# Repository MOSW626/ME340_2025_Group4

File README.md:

# ME340_2025_Group4
`/application` 에는 애플리케이션 개발에 대한 내용 작성\
`/chair` 에는 의자 관련 내용 작성\
  ㄴ 아두이노\
  ㄴ 하드웨어 설계\
  ㄴ 회로 설계\
`\detected_machine` 에는 몸 관련 측정 센서 내용 작성\
  ㄴ 아두이노(src)\
  ㄴ 하드웨어 설계\
  ㄴ 회로 설계

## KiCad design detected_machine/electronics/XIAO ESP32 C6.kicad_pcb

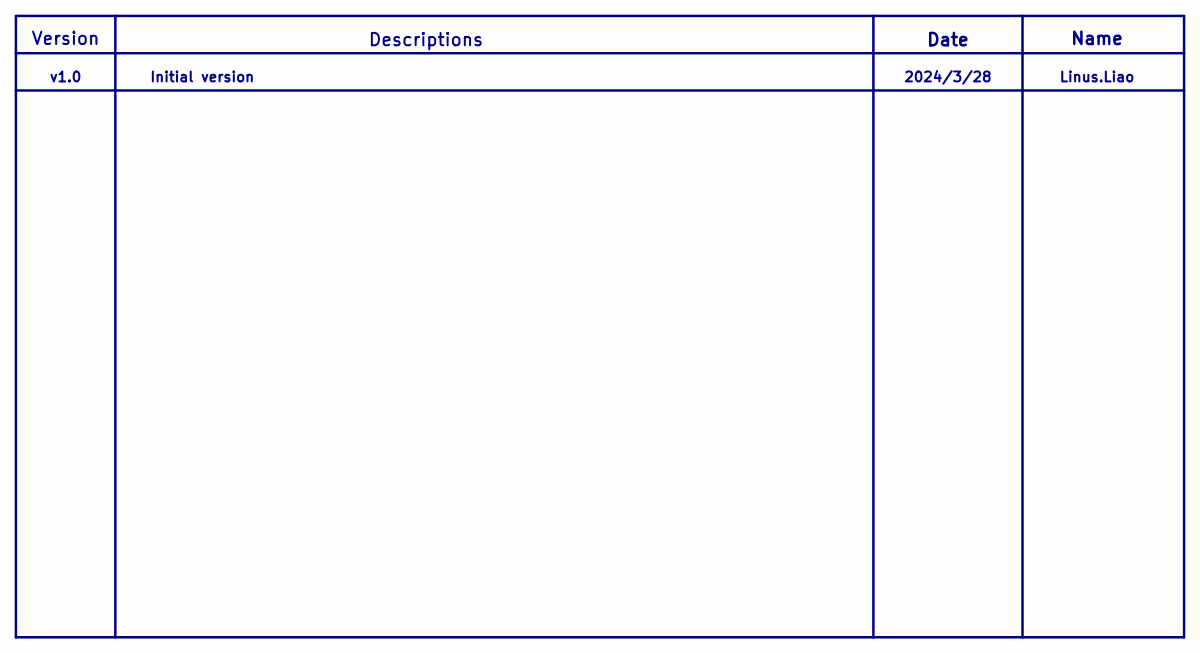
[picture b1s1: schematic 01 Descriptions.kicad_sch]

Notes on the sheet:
Date
Descriptions
Linus.Liao
2024/3/28
v1.0
Initial version
Name
Version

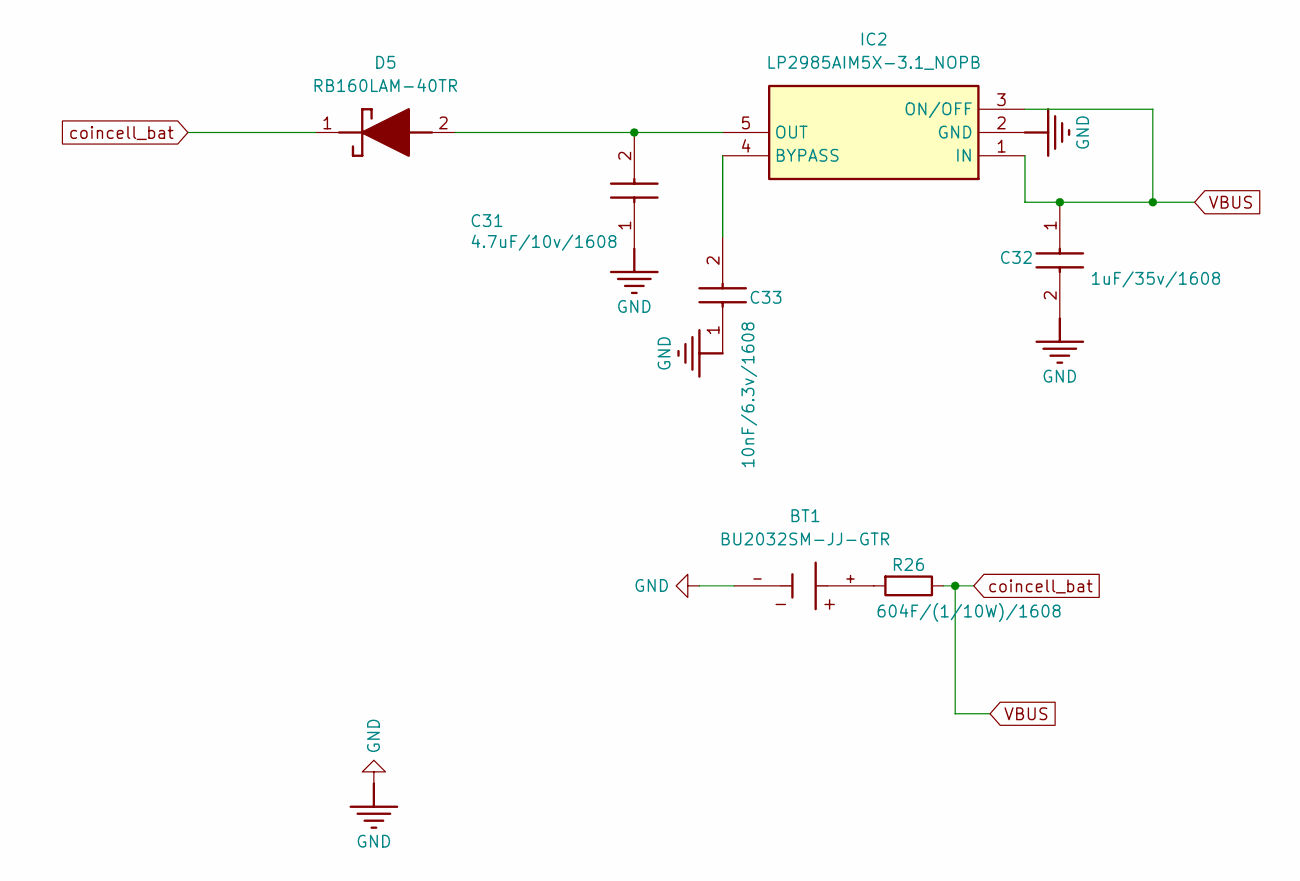
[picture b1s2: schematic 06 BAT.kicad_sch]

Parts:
BT1: BU2032SM-JJ-GTR; BAT_BU2032SM-JJ-GTR; PARTREV H
C31: 4.7uF/10v/1608; C_0603_1608Metric; MANUFACTURER_PART_NUMBER GRM188C71A475KE11D
C32: 1uF/35v/1608; C_0603_1608Metric; MANUFACTURER_PART_NUMBER MBASG168AB7105KTNA01
C33: 10nF/6.3v/1608; C_0603_1608Metric; MANUFACTURER_PART_NUMBER 06036C103KAT2A
D5: RB160LAM-40TR; SODFL4725X105N; Mouser Part Number 755-RB160LAM-40TR
IC2: LP2985AIM5X-3.1_NOPB; SOT95P280X145-5N; Mouser Part Number 926-LP2985AIM5X31NPB
R26: 604F/(1/10W)/1608; R_0603_1608Metric; MANUFACTURER_PART_NUMBER CRCW0603604RFKEAC

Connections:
GND: BT1.-, C31.1, C32.2, C33.1, IC2.2 (GND); also elsewhere on the board
unnamed: BT1.+, R26.2
unnamed: C31.2, D5.2 (A), IC2.5 (OUT)
unnamed: C33.2, IC2.4 (BYPASS)
VBUS: C32.1, D5.1 (K), IC2.1 (IN), IC2.3 (ON/OFF), R26.1; also elsewhere on the board

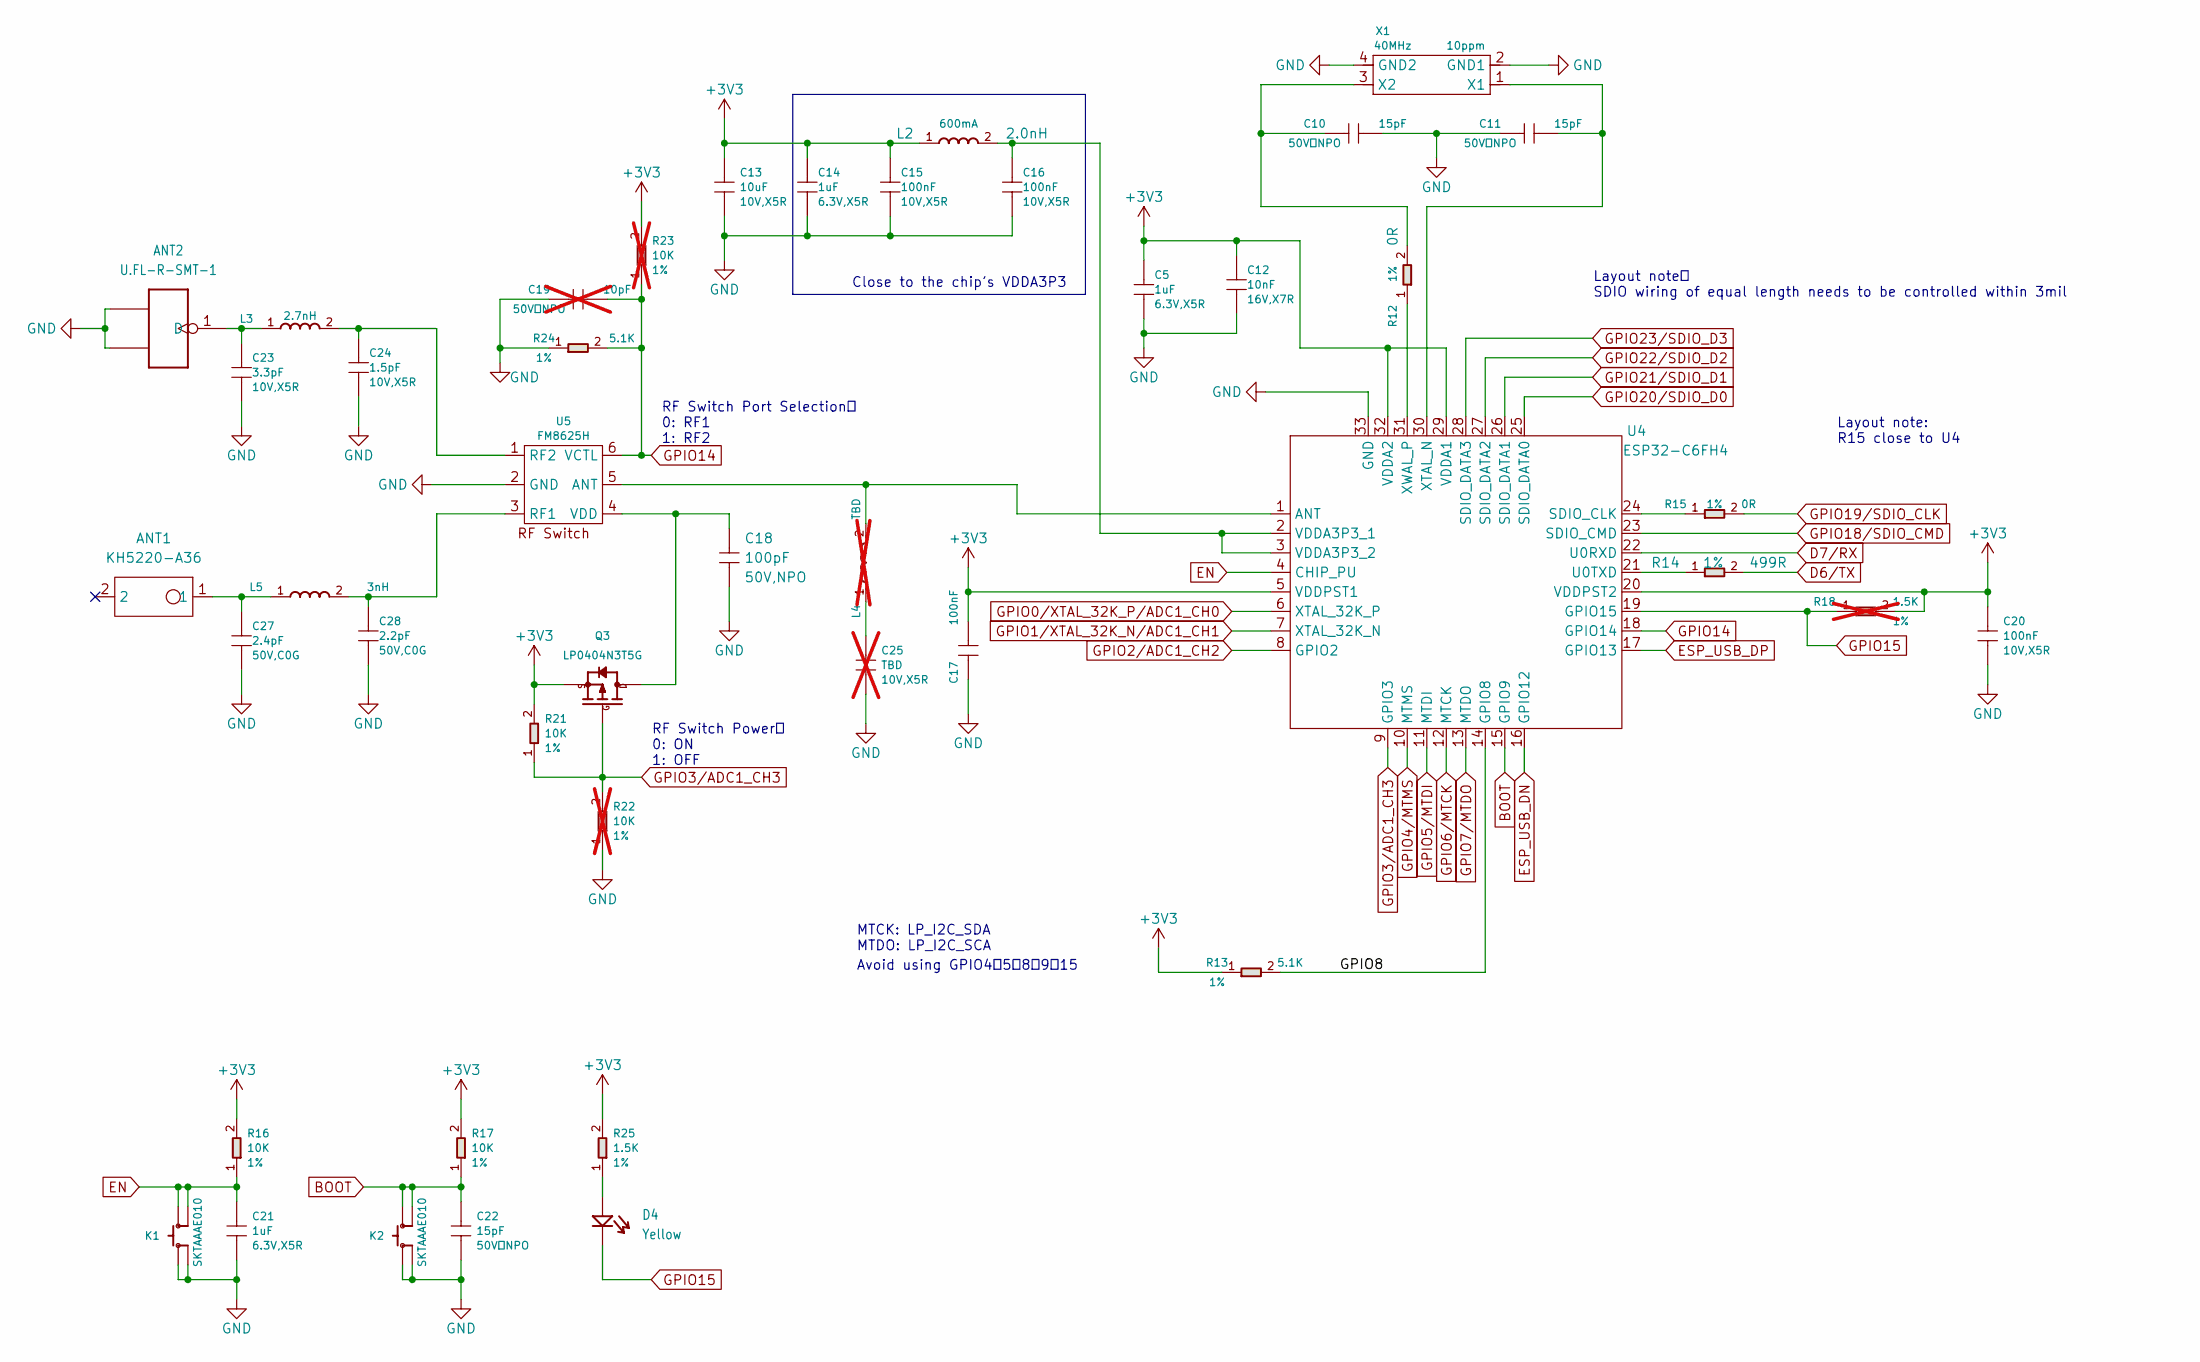
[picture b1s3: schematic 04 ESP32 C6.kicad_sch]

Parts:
ANT1: KH5220-A36; ANT2P-5.2x2x1.1MM; MPN KH5220-A36
ANT2: U.FL-R-SMT-1; U-FL3P-SMD-2.6X2.6X1.0MM; MPN U.FL-R-SMT-1
C5, C14, C21: 1uF; C0201; Voltage Rating 6.3V,X5R; MPN CC0201MRX5R5BB105
C10, C11, C22: 15pF; C0201; Voltage Rating 50V，NPO; MPN CC0201JRNPO9BN150
C12: 10nF; C0201; Voltage Rating 16V,X7R; MPN CC0201KRX7R7BB103
C13: 10uF; C0402; Voltage Rating 10V,X5R; MPN CC0402MRX5R6BB106
C15, C16, C17, C20: 100nF; C0201; Voltage Rating 10V,X5R; MPN CC0201KRX5R6BB104
C18: 100pF; C0201; Voltage Rating 50V,NPO; MPN CC0201JRNPO9BN101
C19: 10pF; C0201; Voltage Rating 50V，NPO; MPN CC0201JRNPO8BN100; not fitted
C23: 3.3pF; C0201; Voltage Rating 10V,X5R; MPN CQ0201BRNPO8BN3R3
C24: 1.5pF; C0201; Voltage Rating 10V,X5R; MPN CC0201BRNPO9BN1R5
C25: TBD; C0201; Voltage Rating 10V,X5R; Part Type Ceramic; not fitted
C27: 2.4pF; C0201; Voltage Rating 50V,C0G; MPN GRM0335C1H2R4BA01D
C28: 2.2pF; C0201; Voltage Rating 50V,C0G; MPN GRM0335C1H2R2BA01D
D4: Yellow; LED-0402; MPN 16-213/Y2C-AN2Q1B/3T
K1, K2: SKTAAAE010; SW4-SMD-2.8-2.6X1.6X0.53MM; MPN SKTAAAE010
L2: 2.0nH; L0201; Rating 600mA; MPN LQP03HQ2N0B02D
L3: 2.7nH; L0201; MPN LQP03TN2N7B02D
L4: TBD; L0201; Part Type L; not fitted
L5: 3nH; L0201; MPN LQP03TN3N0B02D
Q3: LP0404N3T5G; PMOS_1.0X0.6X0.35MM; MPN LP0404N3T5G
R12, R15: 0R; R0201; Power Rating 1%; MPN RC0201FR-070RL
R13, R24: 5.1K; R0201; Power Rating 1%; MPN RC0201FR-075K1L
R14: 499R; R0201; Power Rating 1%; MPN RC0201FR-07499RL
R16, R17, R21: 10K; R0201; Power Rating 1%; MPN RC0201FR-0710KL
R18: 1.5K; R0201; Power Rating 1%; MPN RC0201FR-071K5L; not fitted
R22, R23: 10K; R0201; Power Rating 1%; MPN RC0201FR-0710KL; not fitted
R25: 1.5K; R0201; Power Rating 1%; MPN RC0201FR-071K5L
U4: ESP32-C6FH4; QFN32-0.5-5X5MM; MPN ESP32-C6FH4
U5: FM8625H; DFN6-0.4-1.1X0.7X0.45MM; MPN FM8625H
X1: 40MHz; X4-SMD-1.6X1.2MM; Rating 10ppm; MPN CJ17-400001010B20

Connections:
+3V3: C5.1, C12.1, C13.1, C14.1, C15.1, C17.1, C20.1, L2.1, Q3.2 (S), R13.1, R16.2, R17.2, R18.2, R21.2, R23.2, R25.2, U4.5 (VDDPST1), U4.20 (VDDPST2), U4.29 (VDDA1), U4.32 (VDDA2); also elsewhere on the board
/04 ESP32 C6/GPIO8: R13.2, U4.14 (GPIO8)
BOOT: C22.1, K2.3 (B0), K2.4 (B1), R17.1, U4.15 (GPIO9); also elsewhere on the board
D6/TX: R14.2; also elsewhere on the board
D7/RX: U4.22 (U0RXD); also elsewhere on the board
EN: C21.1, K1.3 (B0), K1.4 (B1), R16.1, U4.4 (CHIP_PU); also elsewhere on the board
ESP_USB_DN: U4.16 (GPIO12); also elsewhere on the board
ESP_USB_DP: U4.17 (GPIO13); also elsewhere on the board
GND: ANT2.2 (GND1), ANT2.3 (GND2), C5.2, C10.2, C11.1, C12.2, C13.2, C14.2, C15.2, C16.2, C17.2, C18.2, C19.1, C20.2, C21.2, C22.2, C23.2, C24.2, C25.2, C27.2, C28.2, K1.1 (A0), K1.2 (A1), K2.1 (A0), K2.2 (A1), R22.1, R24.1, U4.33 (GND), U5.2 (GND), X1.2 (GND1), X1.4 (GND2); also elsewhere on the board
GPIO0/XTAL_32K_P/ADC1_CH0: U4.6 (XTAL_32K_P); also elsewhere on the board
GPIO1/XTAL_32K_N/ADC1_CH1: U4.7 (XTAL_32K_N); also elsewhere on the board
GPIO2/ADC1_CH2: U4.8 (GPIO2); also elsewhere on the board
GPIO3/ADC1_CH3: Q3.1 (G), R21.1, R22.2, U4.9 (GPIO3)
GPIO4/MTMS: U4.10 (MTMS); also elsewhere on the board
GPIO5/MTDI: U4.11 (MTDI); also elsewhere on the board
GPIO6/MTCK: U4.12 (MTCK); also elsewhere on the board
GPIO7/MTDO: U4.13 (MTDO); also elsewhere on the board
GPIO14: C19.2, R23.1, R24.2, U4.18 (GPIO14), U5.6 (VCTL)
GPIO15: D4.2 (-), R18.1, U4.19 (GPIO15)
GPIO18/SDIO_CMD: U4.23 (SDIO_CMD); also elsewhere on the board
GPIO19/SDIO_CLK: R15.2; also elsewhere on the board
GPIO20/SDIO_D0: U4.25 (SDIO_DATA0); also elsewhere on the board
GPIO21/SDIO_D1: U4.26 (SDIO_DATA1); also elsewhere on the board
GPIO22/SDIO_D2: U4.27 (SDIO_DATA2); also elsewhere on the board
GPIO23/SDIO_D3: U4.28 (SDIO_DATA3); also elsewhere on the board
unnamed: ANT1.1, C27.1, L5.1
unnamed: ANT2.1 (D), C23.1, L3.1
unnamed: C25.1, L4.1
unnamed: D4.1 (+), R25.1
unnamed: C18.1, Q3.3 (D), U5.4 (VDD)
unnamed: L4.2, U4.1 (ANT), U5.5 (ANT)
unnamed: R15.1, U4.24 (SDIO_CLK)
unnamed: R14.1, U4.21 (U0TXD)
unnamed: C16.1, L2.2, U4.2 (VDDA3P3_1), U4.3 (VDDA3P3_2)
unnamed: C11.2, U4.30 (XTAL_N), X1.1 (X1)
unnamed: R12.1, U4.31 (XWAL_P)
unnamed: C28.1, L5.2, U5.3 (RF1)
unnamed: C24.1, L3.2, U5.1 (RF2)
unnamed: C10.1, R12.2, X1.3 (X2)

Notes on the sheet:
Avoid using GPIO4、5、8、9、15
RF Switch Power： 0: ON 1: OFF
Layout note: R15 close to U4
Close to the chip's VDDA3P3
Layout note： SDIO wiring of equal length needs to be controlled within 3mil
RF Switch Port Selection： 0: RF1 1: RF2
MTCK: LP_I2C_SDA MTDO: LP_I2C_SCA

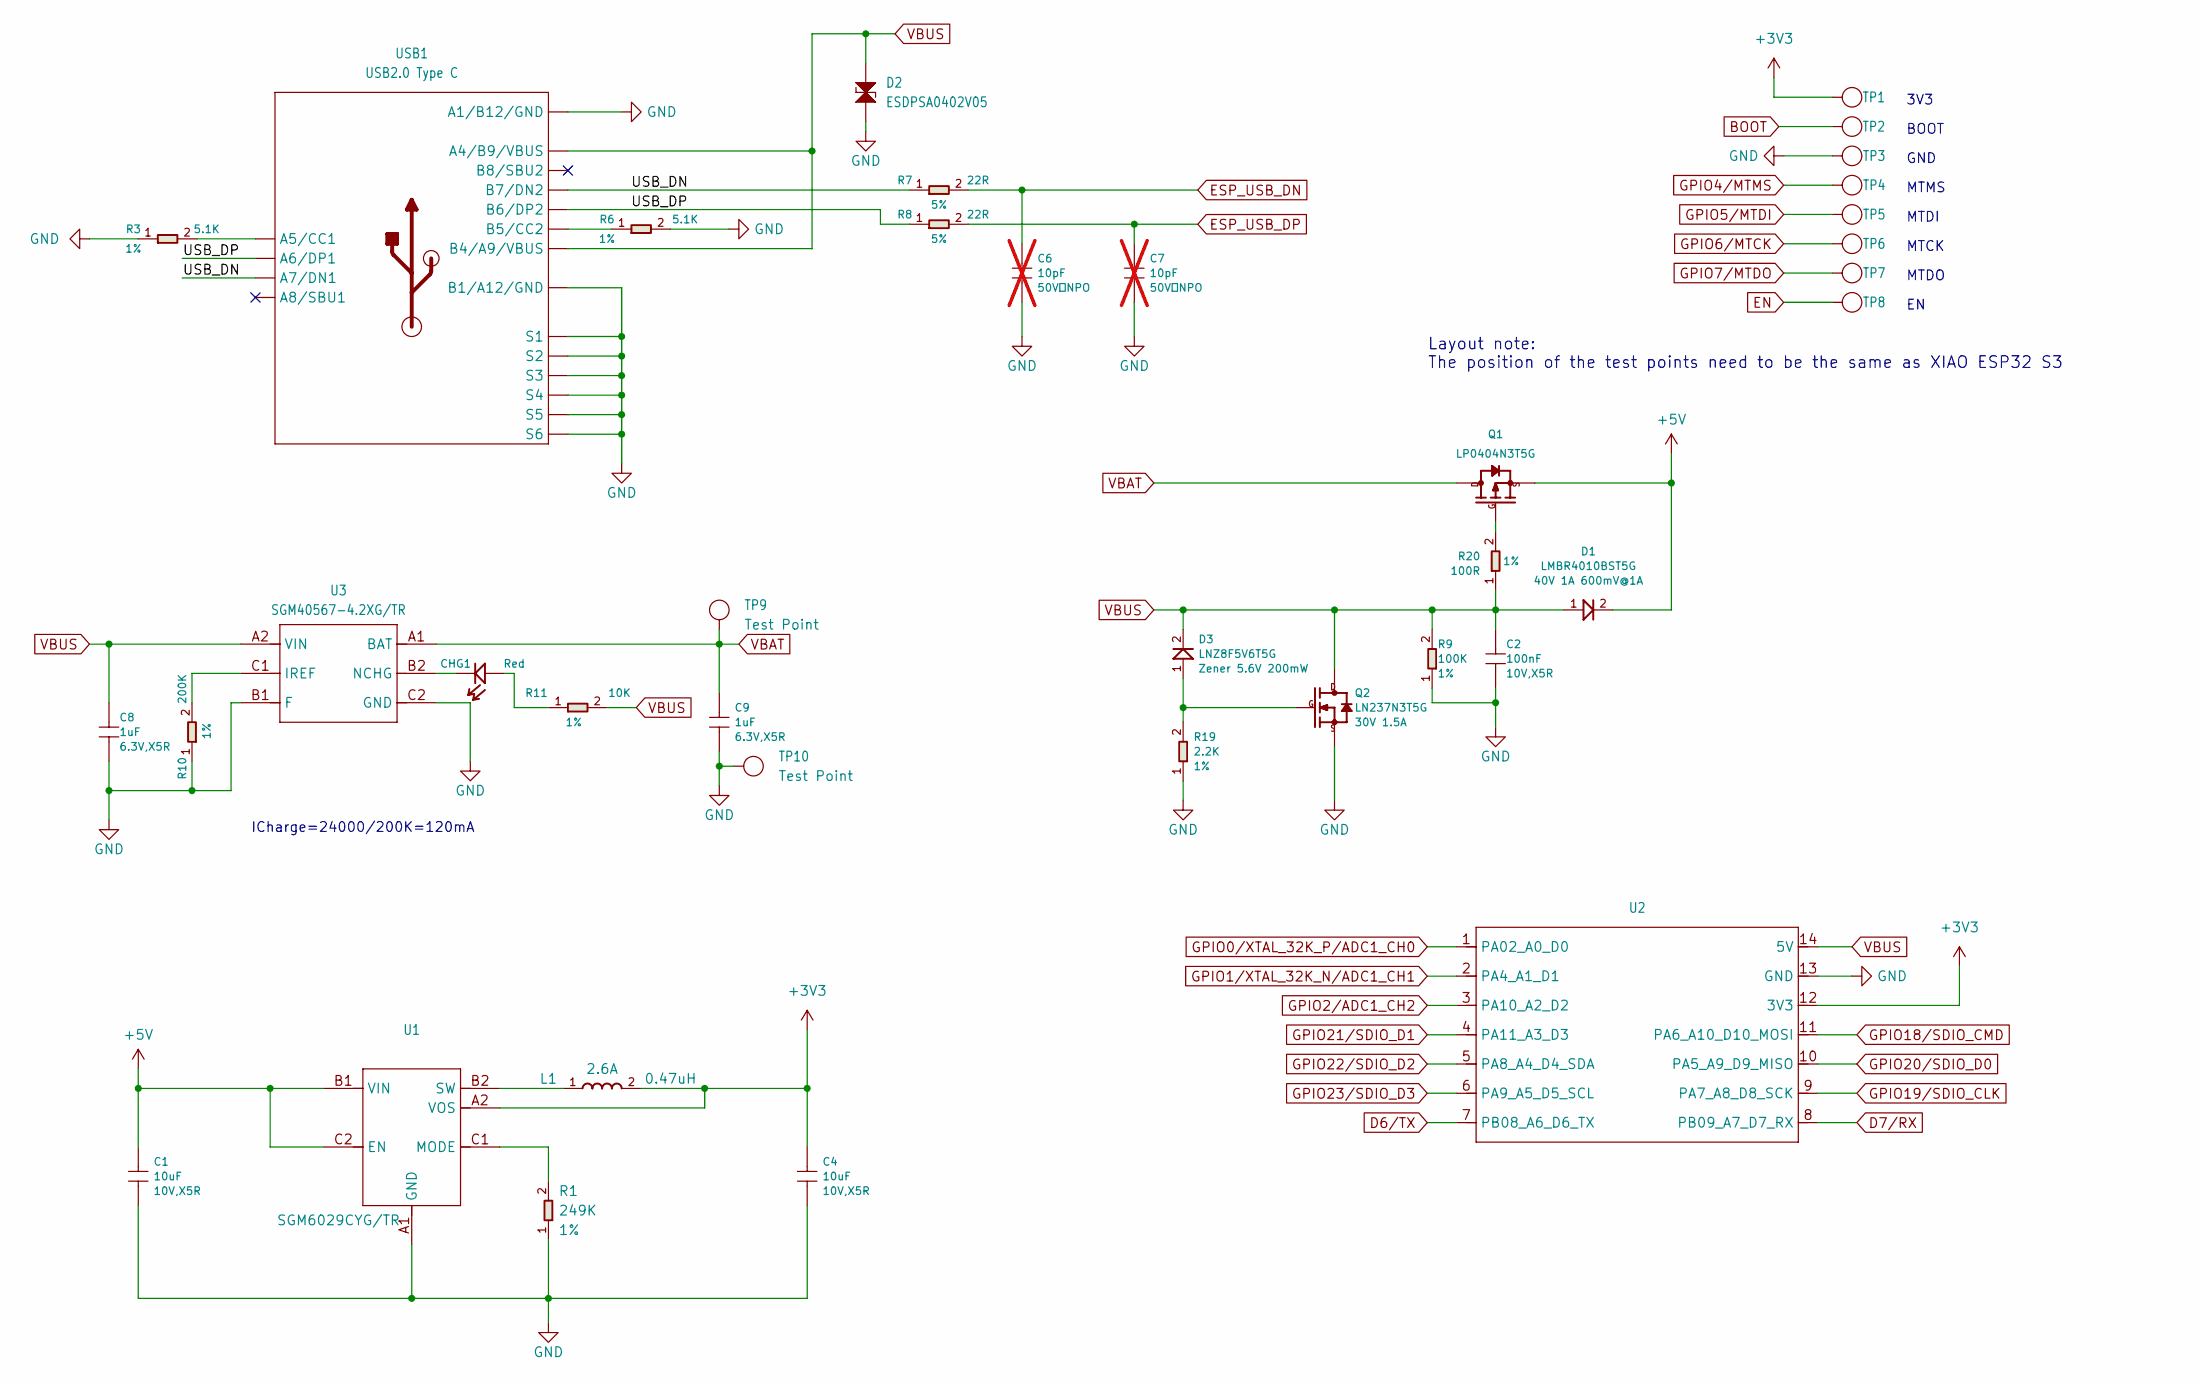
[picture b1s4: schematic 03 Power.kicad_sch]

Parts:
C1, C4: 10uF; C0402; Voltage Rating 10V,X5R; MPN CC0402MRX5R6BB106
C2: 100nF; C0201; Voltage Rating 10V,X5R; MPN CC0201KRX5R6BB104
C6, C7: 10pF; C0201; Voltage Rating 50V，NPO; MPN CC0201JRNPO8BN100; not fitted
C8, C9: 1uF; C0201; Voltage Rating 6.3V,X5R; MPN CC0201MRX5R5BB105
CHG1: Red; LED-0402; MPN BL-HUB37A-AV-TRB
D1: LMBR4010BST5G; DFN1006-2L; Rating 40V 1A 600mV@1A; MPN LMBR4010BST5G
D2: ESDPSA0402V05; ESD-0402; MPN ESDPSA0402V05
D3: LNZ8F5V6T5G; DFN1006-2L; Rating Zener 5.6V 200mW; MPN LNZ8F5V6T5G
L1: 0.47uH; L0603; Rating 2.6A; MPN TFM160808ALC-R47MTAA
Q1: LP0404N3T5G; PMOS_1.0X0.6X0.35MM; MPN LP0404N3T5G
Q2: LN237N3T5G; PMOS_1.0X0.6X0.35MM; Rating 30V 1.5A; MPN LN237N3T5G
R1: 249K; R0201; Power Rating 1%; MPN RC0201FR-07249KL
R3, R6: 5.1K; R0201; Power Rating 1%; MPN RC0201FR-075K1L
R7, R8: 22R; R0201; Power Rating 5%; MPN RC0201JR-0722RL
R9: 100K; R0201; Power Rating 1%; MPN RC0201FR-07100KL
R10: 200K; R0201; Power Rating 1%; MPN RC0201FR-07200KL
R11: 10K; R0201; Power Rating 1%; MPN RC0201FR-0710KL
R19: 2.2K; R0201; Power Rating 1%; MPN RC0201FR-072K2L
R20: 100R; R0201; Power Rating 1%; MPN RC0201FR-07100RL
TP1, TP2, TP3, TP4, TP5, TP6, TP7, TP8: Test Point; TP-D45MIL; Part Type Test Point
TP9, TP10: Test Point; TP-80X40MIL; Part Type Test Point
U1: SMD IC PMIC;DCDC Buck-ADJ-1A,Vin 1.95V to 5.5V,Vo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; BGA6-0.35-0.745X10.95X0.4MM; MPN SGM6029CYG/TR
U2: MOUDLE14P-XIAO-HALF-HOLE
U3: SGM40567-4.2XG/TR; WLCSP-0.4-0.92X1.16X0.4MM; MPN SGM40567-4.2XG/TR
USB1: USB2.0 Type C; USB2.0-TYPE-C; MPN UBF31-0171

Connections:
+3V3: C4.1, L1.2, TP1.1 (T), U1.A2 (VOS), U2.12 (3V3); also elsewhere on the board
+5V: C1.1, D1.2, Q1.2 (S), U1.B1 (VIN), U1.C2 (EN)
/03 Power/USB_DN: R7.1, USB1.A7 (A7/DN1), USB1.B7 (B7/DN2)
/03 Power/USB_DP: R8.1, USB1.A6 (A6/DP1), USB1.B6 (B6/DP2)
BOOT: TP2.1 (T); also elsewhere on the board
D6/TX: U2.7 (PB08_A6_D6_TX); also elsewhere on the board
D7/RX: U2.8 (PB09_A7_D7_RX); also elsewhere on the board
EN: TP8.1 (T); also elsewhere on the board
ESP_USB_DN: C6.1, R7.2; also elsewhere on the board
ESP_USB_DP: C7.1, R8.2; also elsewhere on the board
GND: C1.2, C2.2, C4.2, C6.2, C7.2, C8.2, C9.2, D2.1, Q2.2 (S), R1.1, R3.1, R6.2, R9.1, R10.1, R19.1, TP3.1 (T), TP10.1, U1.A1 (GND), U2.13 (GND), U3.B1 (F), U3.C2 (GND), USB1.A1_B12 (A1/B12/GND), USB1.B1_A12 (B1/A12/GND), USB1.S1, USB1.S2, USB1.S3, USB1.S4, USB1.S5, USB1.S6; also elsewhere on the board
GPIO0/XTAL_32K_P/ADC1_CH0: U2.1 (PA02_A0_D0); also elsewhere on the board
GPIO1/XTAL_32K_N/ADC1_CH1: U2.2 (PA4_A1_D1); also elsewhere on the board
GPIO2/ADC1_CH2: U2.3 (PA10_A2_D2); also elsewhere on the board
GPIO4/MTMS: TP4.1 (T); also elsewhere on the board
GPIO5/MTDI: TP5.1 (T); also elsewhere on the board
GPIO6/MTCK: TP6.1 (T); also elsewhere on the board
GPIO7/MTDO: TP7.1 (T); also elsewhere on the board
GPIO18/SDIO_CMD: U2.11 (PA6_A10_D10_MOSI); also elsewhere on the board
GPIO19/SDIO_CLK: U2.9 (PA7_A8_D8_SCK); also elsewhere on the board
GPIO20/SDIO_D0: U2.10 (PA5_A9_D9_MISO); also elsewhere on the board
GPIO21/SDIO_D1: U2.4 (PA11_A3_D3); also elsewhere on the board
GPIO22/SDIO_D2: U2.5 (PA8_A4_D4_SDA); also elsewhere on the board
GPIO23/SDIO_D3: U2.6 (PA9_A5_D5_SCL); also elsewhere on the board
unnamed: CHG1.1 (+), R11.1
unnamed: CHG1.2 (-), U3.B2 (NCHG)
unnamed: Q1.1 (G), R20.2
unnamed: D3.1, Q2.1 (G), R19.2
unnamed: R1.2, U1.C1 (MODE)
unnamed: L1.1, U1.B2 (SW)
unnamed: R10.2, U3.C1 (IREF)
unnamed: R3.2, USB1.A5 (A5/CC1)
unnamed: R6.1, USB1.B5 (B5/CC2)
VBAT: C9.1, Q1.3 (D), TP9.1, U3.A1 (BAT)
VBUS: C2.1, C8.1, D1.1, D2.2, D3.2, Q2.3 (D), R9.2, R11.2, R20.1, U2.14 (5V), U3.A2 (VIN), USB1.A4_B9 (A4/B9/VBUS), USB1.B4_A9 (B4/A9/VBUS); also elsewhere on the board

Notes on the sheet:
MTMS
MTDI
ICharge=24000/200K=120mA
GND
MTDO
Layout note: The position of the test points need to be the same as XIAO ESP32 S3
MTCK
BOOT
3V3

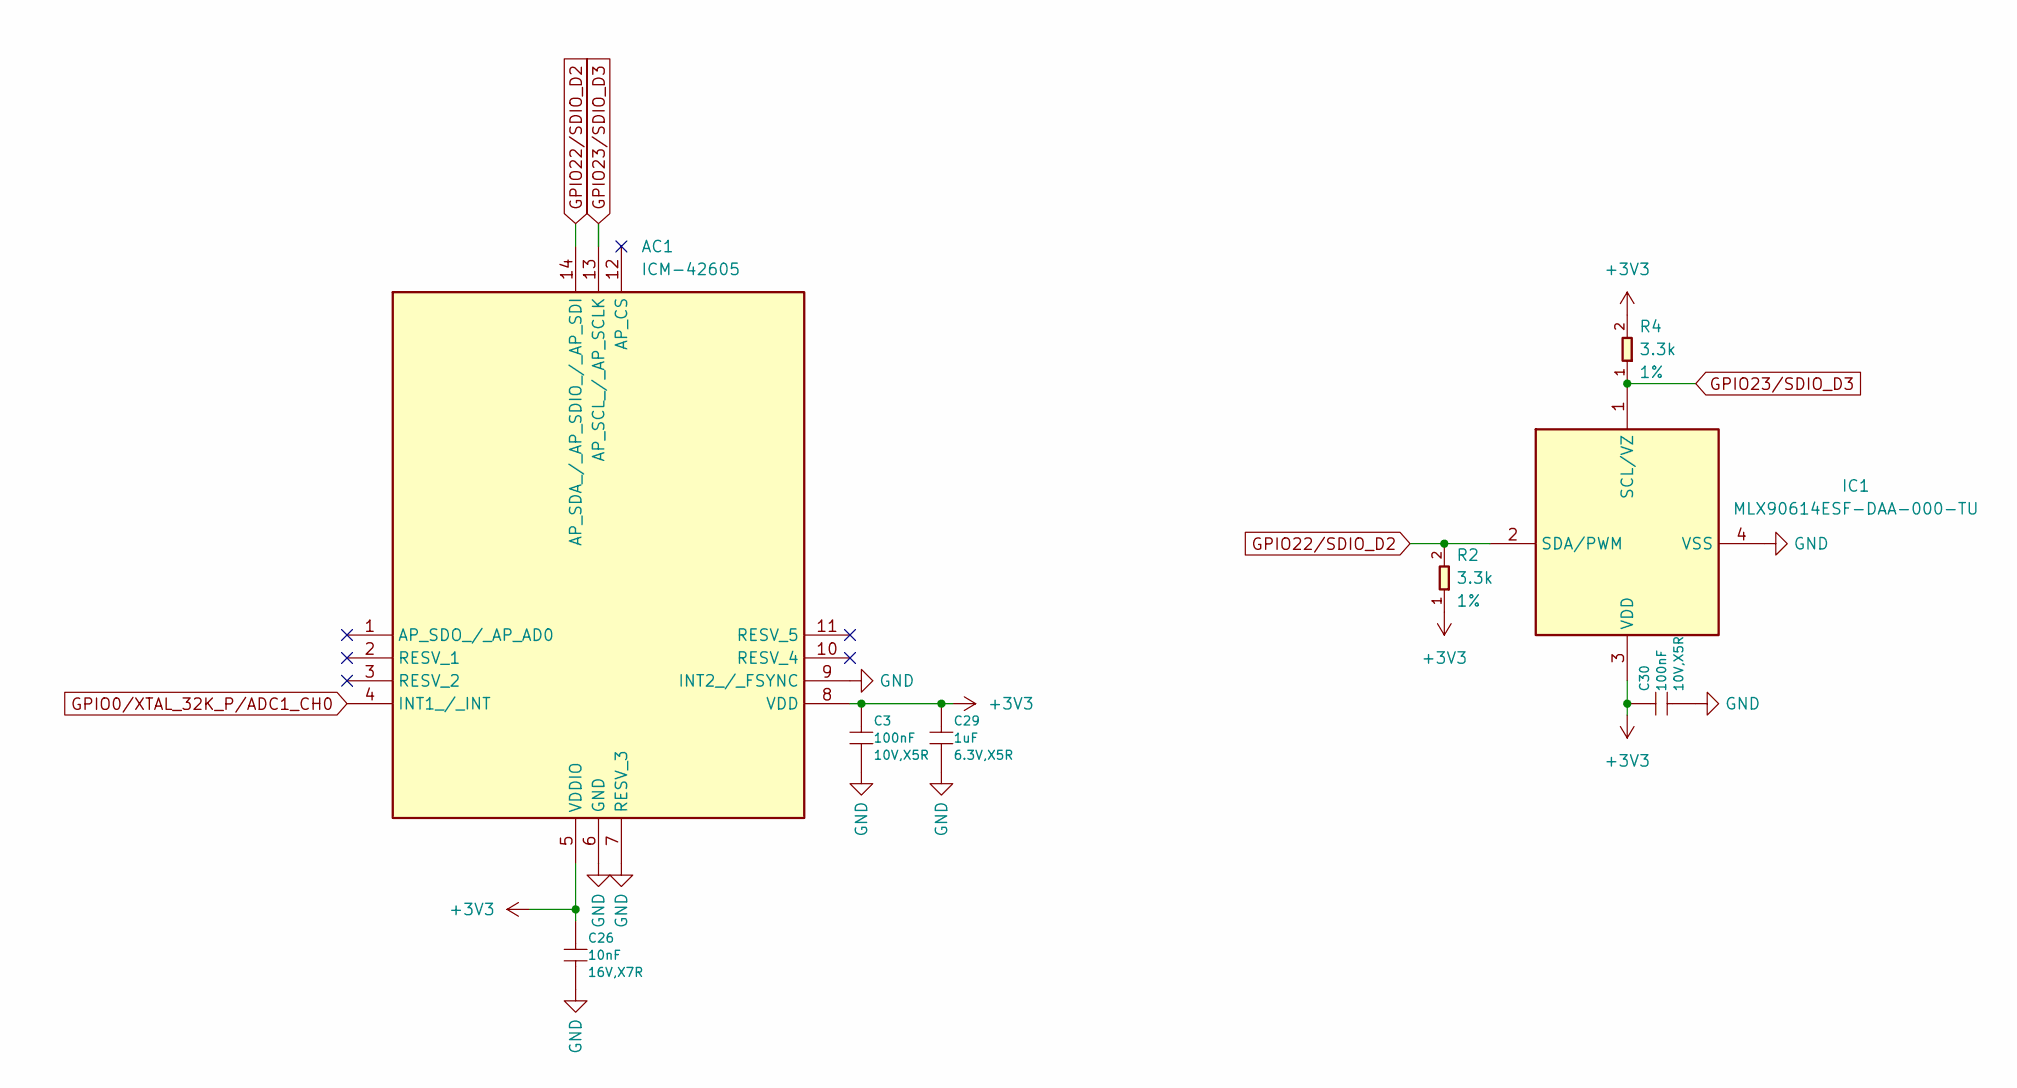
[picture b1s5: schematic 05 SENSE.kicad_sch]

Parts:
AC1: ICM-42605; IIM42352; Mouser Part Number 410-ICM-42605
C3, C30: 100nF; C_0201_0603Metric; Voltage Rating 10V,X5R; MPN CC0201KRX5R6BB104
C26: 10nF; C_0201_0603Metric; Voltage Rating 16V,X7R; MPN CC0201KRX7R7BB103
C29: 1uF; C_0201_0603Metric; Voltage Rating 6.3V,X5R; MPN CC0201MRX5R5BB105
IC1: MLX90614ESF-DAA-000-TU; MLX90614ESFDAA000TU; Mouser Part Number 482-90614ESFDAA000TU
R2, R4: 3.3k; C_0201_0603Metric; Power Rating 1%; MPN 0201WMF3301TEE

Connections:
+3V3: AC1.5 (VDDIO), AC1.8 (VDD), C3.1, C26.1, C29.1, C30.1, IC1.3 (VDD), R2.1, R4.2; also elsewhere on the board
GND: AC1.6 (GND), AC1.7 (RESV_3), AC1.9 (INT2_/_FSYNC), C3.2, C26.2, C29.2, C30.2, IC1.4 (VSS); also elsewhere on the board
GPIO0/XTAL_32K_P/ADC1_CH0: AC1.4 (INT1_/_INT); also elsewhere on the board
GPIO22/SDIO_D2: AC1.14 (AP_SDA_/_AP_SDIO_/_AP_SDI), IC1.2 (SDA/PWM), R2.2; also elsewhere on the board
GPIO23/SDIO_D3: AC1.13 (AP_SCL_/_AP_SCLK), IC1.1 (SCL/VZ), R4.1; also elsewhere on the board

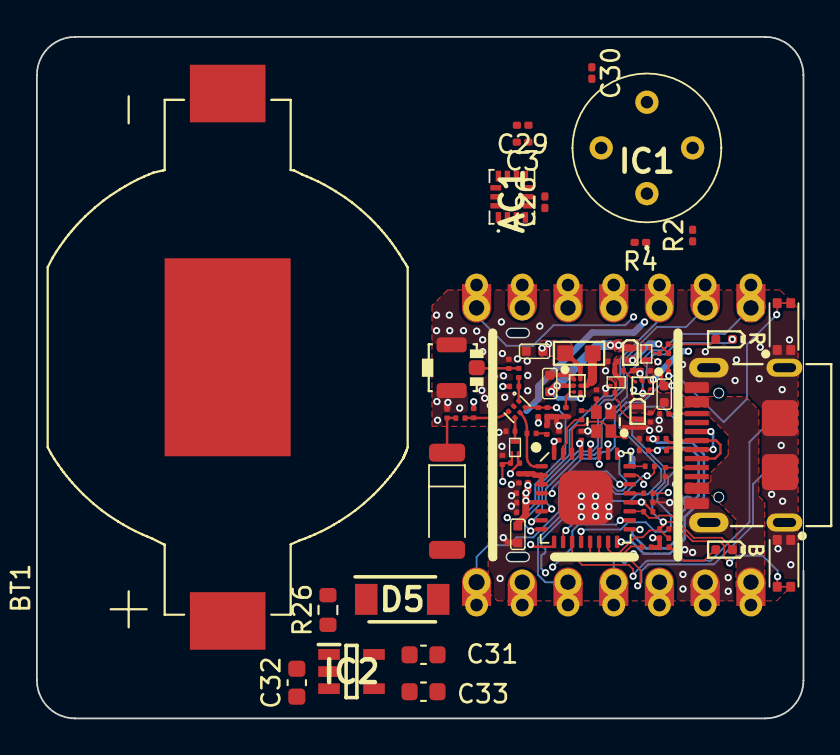
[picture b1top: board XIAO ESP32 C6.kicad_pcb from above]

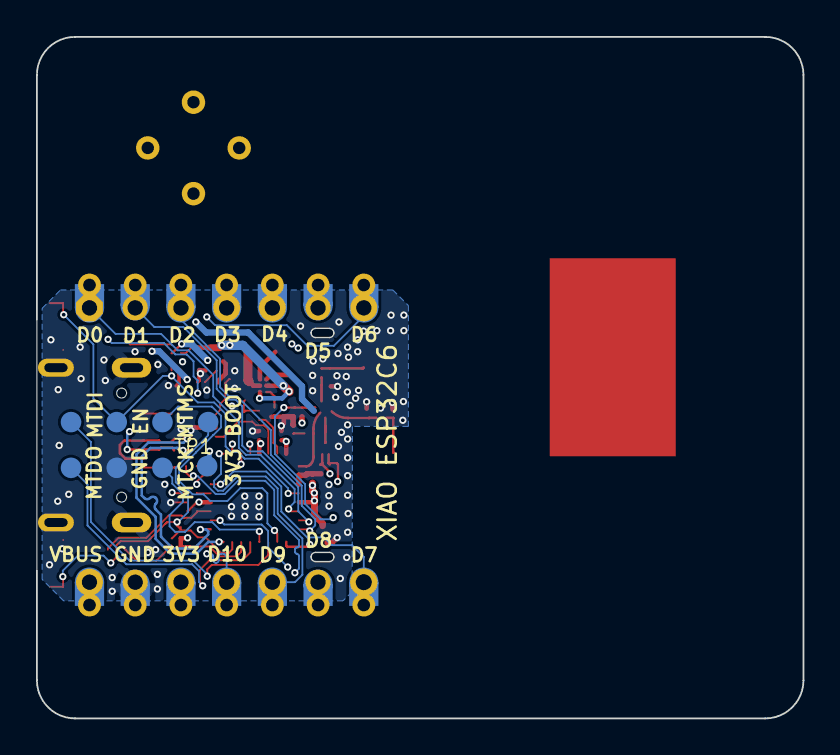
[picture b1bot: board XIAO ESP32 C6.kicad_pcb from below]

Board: 4 copper layers, 42.6 x 37.9 mm, 95 parts (8 on the bottom side), 56 nets.

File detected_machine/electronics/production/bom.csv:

Designator,Footprint,Quantity,Value,LCSC Part #
AC1,IIM42352,1,ICM-42605,
ANT1,ANT2P-5.2x2x1.1MM,1,KH5220-A36,KH5220-A36
ANT2,U-FL3P-SMD-2.6X2.6X1.0MM,1,U.FL-R-SMT-1,U.FL-R-SMT-1
BT1,BAT_BU2032SM-JJ-GTR,1,BU2032SM-JJ-GTR,
"C1, C13, C4",C0402,3,10uF,CC0402MRX5R6BB106
"C10, C11, C22",C0201,3,15pF,CC0201JRNPO9BN150
C12,C0201,1,10nF,CC0201KRX7R7BB103
"C14, C21, C5, C8, C9",C0201,5,1uF,CC0201MRX5R5BB105
"C15, C16, C17, C2, C20",C0201,5,100nF,CC0201KRX5R6BB104
C18,C0201,1,100pF,CC0201JRNPO9BN101
"C19, C6, C7",C0201,3,10pF,CC0201JRNPO8BN100
C23,C0201,1,3.3pF,CQ0201BRNPO8BN3R3
C24,C0201,1,1.5pF,CC0201BRNPO9BN1R5
C25,C0201,1,TBD,
C26,0201,1,10nF,CC0201KRX7R7BB103
C27,C0201,1,2.4pF,GRM0335C1H2R4BA01D
C28,C0201,1,2.2pF,GRM0335C1H2R2BA01D
C29,0201,1,1uF,CC0201MRX5R5BB105
"C3, C30",0201,2,100nF,CC0201KRX5R6BB104
C31,0603,1,4.7uF/10v/1608,
C32,0603,1,1uF/35v/1608,
C33,0603,1,10nF/6.3v/1608,
CHG1,LED-0402,1,Red,BL-HUB37A-AV-TRB
D1,DFN1006-2L,1,LMBR4010BST5G,LMBR4010BST5G
D2,ESD-0402,1,ESDPSA0402V05,ESDPSA0402V05
D3,DFN1006-2L,1,LNZ8F5V6T5G,LNZ8F5V6T5G
D4,LED-0402,1,Yellow,16-213/Y2C-AN2Q1B/3T
D5,SODFL4725X105N,1,RB160LAM-40TR,
IC1,MLX90614ESFDAA000TU,1,MLX90614ESF-DAA-000-TU,
IC2,SOT95P280X145-5N,1,LP2985AIM5X-3.1_NOPB,
"K1, K2",SW4-SMD-2.8-2.6X1.6X0.53MM,2,SKTAAAE010,SKTAAAE010
L1,L0603,1,0.47uH,TFM160808ALC-R47MTAA
L2,L0201,1,2.0nH,LQP03HQ2N0B02D
L3,L0201,1,2.7nH,LQP03TN2N7B02D
L4,L0201,1,TBD,
L5,L0201,1,3nH,LQP03TN3N0B02D
"Q1, Q3",PMOS_1.0X0.6X0.35MM,2,LP0404N3T5G,LP0404N3T5G
Q2,PMOS_1.0X0.6X0.35MM,1,LN237N3T5G,LN237N3T5G
R1,R0201,1,249K,RC0201FR-07249KL
R10,R0201,1,200K,RC0201FR-07200KL
"R11, R16, R17, R21, R22, R23",R0201,6,10K,RC0201FR-0710KL
"R12, R15",R0201,2,0R,RC0201FR-070RL
"R13, R24, R3, R6",R0201,4,5.1K,RC0201FR-075K1L
R14,R0201,1,499R,RC0201FR-07499RL
"R18, R25",R0201,2,1.5K,RC0201FR-071K5L
R19,R0201,1,2.2K,RC0201FR-072K2L
"R2, R4",0201,2,3.3k,0201WMF3301TEE
R20,R0201,1,100R,RC0201FR-07100RL
R26,0603,1,604F/(1/10W)/1608,
"R7, R8",R0201,2,22R,RC0201JR-0722RL
R9,R0201,1,100K,RC0201FR-07100KL
"TP1, TP2, TP3, TP4, TP5, TP6, TP7, TP8",TP-D45MIL,8,Test Point,
U1,BGA6-0.35-0.745X10.95X0.4MM,1,"SMD IC PMIC;DCDC Buck-ADJ-1A,Vin 1.95V to 5.5V,Vout 1.8V to 3.3V;WLCSP-6B",SGM6029CYG/TR	
U2,MOUDLE14P-XIAO-HALF-HOLE,1,~,
U3,WLCSP-0.4-0.92X1.16X0.4MM,1,SGM40567-4.2XG/TR,SGM40567-4.2XG/TR
U4,QFN32-0.5-5X5MM,1,ESP32-C6FH4,ESP32-C6FH4
U5,DFN6-0.4-1.1X0.7X0.45MM,1,FM8625H,FM8625H
USB1,USB2.0-TYPE-C,1,USB2.0 Type C,UBF31-0171
X1,X4-SMD-1.6X1.2MM,1,40MHz,CJ17-400001010B20

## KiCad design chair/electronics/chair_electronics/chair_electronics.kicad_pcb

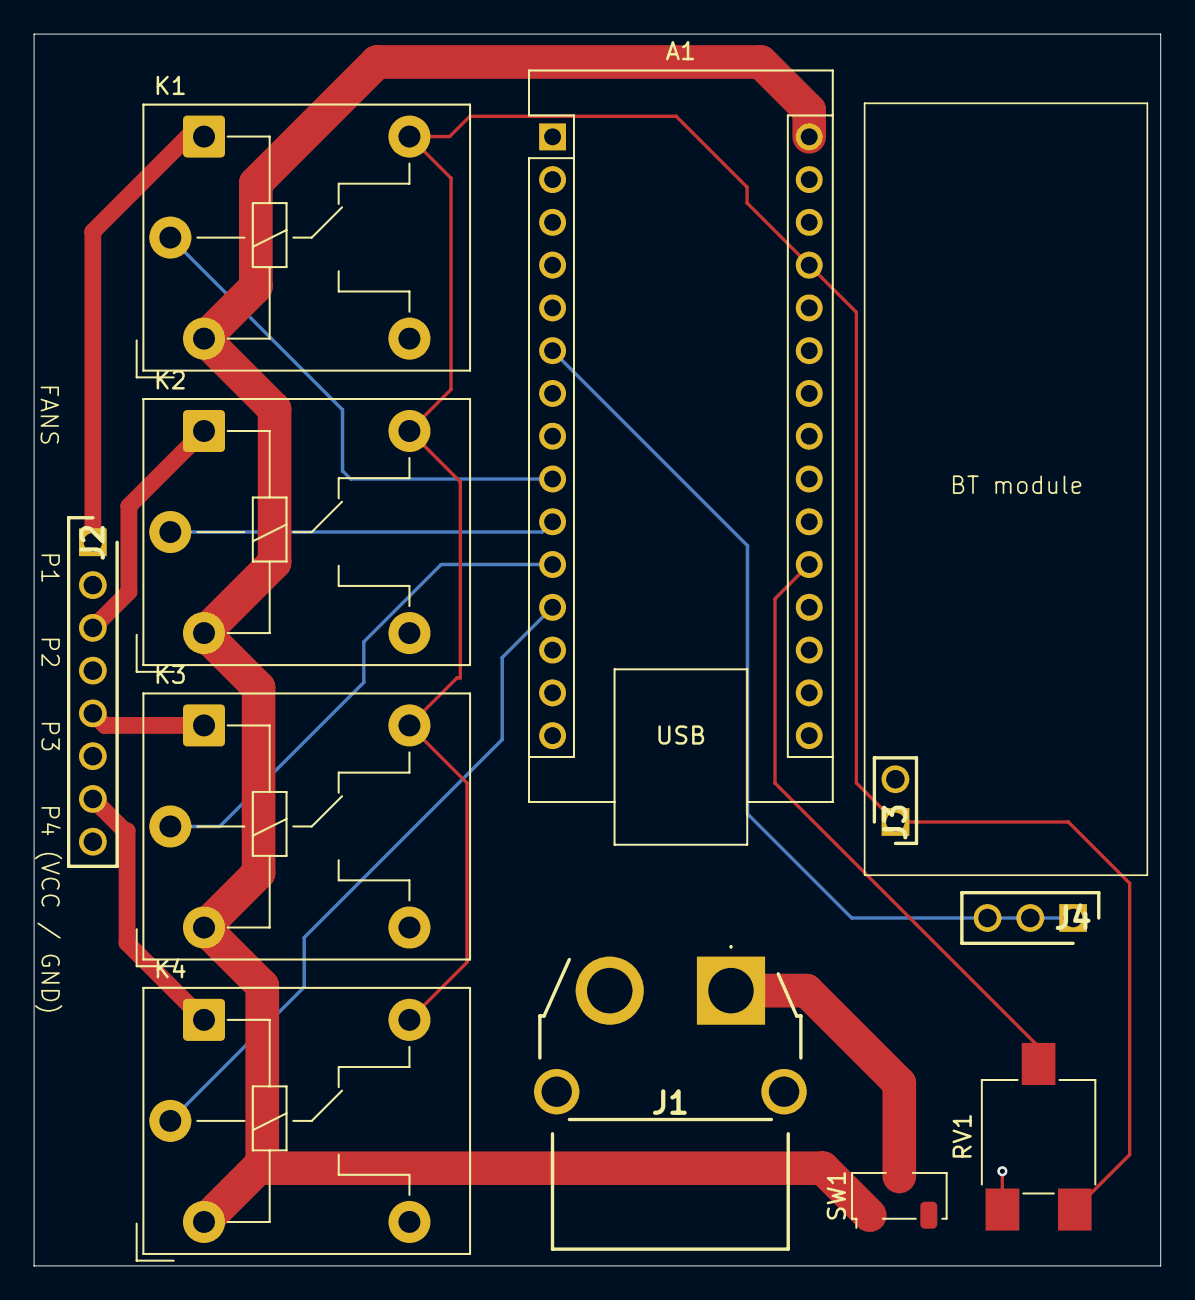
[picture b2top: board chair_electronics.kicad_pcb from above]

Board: 2 copper layers, 66.9 x 73.1 mm, 11 parts (0 on the bottom side), 14 nets.

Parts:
A1: Arduino_Nano_v3.x; Arduino_Nano
J1: XT60PW-F; XT60PWF
J2: PH1-08-UA; HDRV8W64P0X254_1X8_2032X250X888P
J3: PH1-02-UA; HDRV2W64P0X254_1X2_508X250X850P
J4: PH1-03-UA; HDRV3W64P0X254_1X3_762X250X952P
K1, K2, K3, K4: JQC-3FF-012-1Z; Relay_SPDT_Hongfa_JQC-3FF_0XX-1Z
RV1: R_Potentiometer; Potentiometer_ACP_CA6-VSMD_Vertical
SW1: SW_Nidec_CAS-120A1; Nidec_Copal_CAS-120A

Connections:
+5V: A1.27 (+5V), J3.1, K1.12, K2.12, K3.12, K4.12, RV1.1
/FAN: A1.6 (D3), J4.1, J4.2, J4.3
/P1: J2.1, K1.A1
/P2: J2.3, K2.A1
/P3: J2.5, K3.A1
/P4: J2.7, K4.A1
/R1: A1.9 (D6), K1.11
/R2: A1.10 (D7), K2.11
/R3: A1.11 (D8), K3.11
/R4: A1.12 (D9), K4.11
GND: A1.4 (GND), A1.29 (GND), J1.2, J2.2, J2.4, J2.6, J2.8, J3.2, K1.14, K2.14, K3.14, K4.14, RV1.3
unnamed: A1.20 (A1), RV1.2
VCC: A1.30 (VIN), K1.A2, K2.A2, K3.A2, K4.A2, SW1.1 (C)
VIN: J1.1, SW1.2 (B)

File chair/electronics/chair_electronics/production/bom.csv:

Designator,Footprint,Quantity,Value,LCSC Part #
A1,Arduino_Nano,1,Arduino_Nano_v3.x,
J1,XT60PWF,1,XT60PW-F,
J2,HDRV8W64P0X254_1X8_2032X250X888P,1,PH1-08-UA,
J3,HDRV2W64P0X254_1X2_508X250X850P,1,PH1-02-UA,
J4,HDRV3W64P0X254_1X3_762X250X952P,1,PH1-03-UA,
"K1, K2, K3, K4",Relay_SPDT_Hongfa_JQC-3FF_0XX-1Z,4,JQC-3FF-012-1Z,
RV1,Potentiometer_ACP_CA6-VSMD_Vertical,1,R_Potentiometer,
SW1,Nidec_Copal_CAS-120A,1,SW_Nidec_CAS-120A1,

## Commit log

2025-11-19 setting
2025-11-19 빈 폴더 구조 추가 (.gitkeep 파일 포함)
2025-11-19 Add Arduino Nano control code for fan and peltier management
2025-11-24 Update Arduino Nano code to modify pin assignments and enhance fan and peltier control logic
2025-11-24 Update README.md to include application and chair section details, along with detected machine sensor information
2025-11-25 modified: README.md
2025-11-26 Update .vscode/colcon.env to modify environment variables including CURSOR_TRACE_ID, VSCODE_CODE_CACHE_PATH, and VSCODE_IPC_HOOK
2025-11-26 Refactor README.md to improve formatting of application, chair, and detected machine sections for better readability
2025-11-26 Remove project_modify.ino file, which contained the implementation for sensor data handling and BLE communication.
2025-11-26 add test file
2025-11-26 add files
2025-11-26 test
2025-11-26 sensor value (8, string) modified version
2025-12-03 Permission added (Read media audio)
2025-12-03 Add the acc. detector (RMS(acc x, y, z))
2025-12-05 Modified the code (Bluetooth -> BLE), ESP32 UUID
2025-12-05 스피커 연결은 바로가기로 수정 앱 내 블루투스 연결은 ESP32 센서 연결로 수정
2025-12-05 ESP32 UUID 수정
2025-12-05 Add vertical scroll ESP32, 스피커 연결 box 구분
2025-12-05 connecting ESP32 ver.BLE (before ver.wifi)
2025-12-05 Add permission (internet)
2025-12-05 ESP32 ver.wifi
2025-12-05 ESP32 ver.BLE (연결까지 완)
2025-12-06 Modified sensor graph (Add the max, min temp, and grid)
2025-12-06 Modified date data location, and grid (horizontal line)
2025-12-06 Add colors
2025-12-06 Electronics
2025-12-07 Add files via upload
    demo app apk file uploaded
2025-12-07 낙상, 고열 구분하여 비프음 변경 플레이리스트 수정
